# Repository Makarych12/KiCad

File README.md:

# KiCad Мастер Pro

Интерактивный курс проектирования печатных плат в KiCad 8–10: статический сайт (PWA) и serverless API для Vercel.

## Развёртывание на Vercel

1. **Импорт репозитория.** На [vercel.com/new](https://vercel.com/new) выберите репозиторий `Makarych12/KiCad`. Framework Preset: **Other**. Build Command и Output Directory оставьте пустыми: сайт статический, функции лежат в `api/`.
2. **Хранилище.** Project → Storage → Marketplace → **Upstash Redis** (это бывший Vercel KV) → Connect к проекту. Vercel сам добавит переменные `KV_REST_API_URL` и `KV_REST_API_TOKEN`.
3. **AI-ассистент.** Project → Settings → Environment Variables → `OPENROUTER_API_KEY` (ключ `sk-or-…` с openrouter.ai/keys) **или** `ANTHROPIC_API_KEY` (console.anthropic.com). Модель по умолчанию — Claude Opus 5 (`anthropic/claude-opus-5` на OpenRouter); другую можно задать через `KM_MODEL`. Необязательно, без ключа сайт работает.
4. **Deploy** или Redeploy после добавления переменных. Каждый следующий `git push` в `main` деплоится автоматически.
5. **Проверка.** Откройте `https://<ваш-проект>.vercel.app/api/health`. Должно быть `"storage":"redis"` и, если задан ключ, `"ai":true`.

**Выбор модели.** На странице `/models` посетитель выбирает модель для ассистента. Сайт разрешает только модели не дороже `KM_MAX_PRICE` долларов за 1 млн токенов вывода (по умолчанию 30). Можно задать и явный список `KM_ALLOWED_MODELS`, например `anthropic/*,google/gemini-2.5-flash`. Так посетители не потратят баланс ключа на дорогие модели.

Все переменные описаны в `.env.example`. Если Redis не подключён, API работает, но данные живут только в памяти функции и пропадают при перезапуске. Статус «хранилище в памяти» виден в Настройках сайта.

### API (`api/*.js`, общий код — `lib/`)

| Эндпоинт | Методы | Назначение |
|---|---|---|
| `/api/chat` | POST | AI-ассистент (Claude через Anthropic или OpenRouter, потоковый ответ SSE) |
| `/api/messages` | GET `?since=`, POST | Чат сообщества (опрос раз в 4 с) |
| `/api/leaderboard` | GET, POST | Таблица лидеров |
| `/api/submit-project` | GET, POST, POST `?action=rate&id=` | Галерея проектов и рейтинг |
| `/api/file` | GET `?id=&kind=` | Скачивание файлов галереи |
| `/api/sync` | GET, PUT | Синхронизация прогресса |
| `/api/register` | GET, POST | Вход по нику (токен) |
| `/api/newsletter` | POST | Подписка на рассылку |
| `/api/models` | GET | Каталог моделей OpenRouter с отметкой доступности (кэш 1 ч) |
| `/api/health` | GET | Состояние (AI, провайдер, тип хранилища) |

У всех эндпоинтов CORS: по умолчанию `*`, ограничить можно через `ALLOWED_ORIGIN`. Лимиты частоты считаются в Redis.

## Локальный запуск

```bash
npm install
npm run dev                      # http://localhost:8080 — статика + те же функции из api/
OPENROUTER_API_KEY=sk-or-... npm run dev   # или ANTHROPIC_API_KEY=sk-ant-...
npm run test:api                 # тест всех эндпоинтов: с имитацией Upstash Redis и с локальным хранилищем
```

Локально без Redis данные сохраняются в `.data/db.json`. Переменные можно положить в `.env`: сервер прочитает его сам.

## Что внутри

| Раздел | Где | Что сделано |
|---|---|---|
| 1. Уроки | `data/lessons*.js` | 56 уроков (44 базовых, 8 продвинутых, 4 бонусных): шаги, аннотированные иллюстрации, советы, ошибки, тест из 5 вопросов |
| 2. Видео | `data/demos.js`, `js/views/demos.js` | 8 анимированных демонстраций: главы, пауза, перемотка, скорость 0,25–2×. Можно подключить настоящие mp4 |
| 3. Практика | `tools/projects.py` → `kicad/pXX*` | 16 проектов: заготовка KiCad, эталон, автопроверка netlist по цепям и номиналам, медали |
| 4. Компоненты | `data/components.js` | 1182 позиции: 174 описаны вручную, остальное — ряды E24/E6, стабилитроны, светодиоды, разъёмы |
| 5. Шаблоны | `tools/circuits.py` → `kicad/t-*` | 26 проектов KiCad: .kicad_pro/.kicad_sch, PDF, BOM, SVG-превью, netlist |
| 6. Симулятор | `js/sim.js`, `js/views/sim.js` | Метод узловых потенциалов, Ньютон для диодов и светодиодов, переходные процессы для конденсаторов |
| Gerber и 3D | `js/gerber-parse.js`, `js/views/gerber.js` | Разбор Gerber RS-274X/X2 (макросы, дуги, полигоны), Excellon и ZIP в браузере; виды «Верх», «Низ», «Слои», 3D; линейка; проверка перед заказом. Демо-платы — настоящие Gerber из KiCad (`tools/pcbgen.py`) |
| Тренажёр трассировки | `js/routing-engine.js`, `js/views/routing.js` | 5 уровней: дорожки под 45°, зазоры, силовые цепи, два слоя и переходы, DRC и проверка связности, звёзды и опыт |
| 7. Тесты | в уроках | Очки, медали, достижения, таблица лидеров (через сервер) |
| 8. История | `data/history.js` | 5 статей, хронология, персоналии |
| 9. Справочник | `data/reference.js`, `js/views/reference.js` | Горячие клавиши, ряды E, цветовой код, типоразмеры, слои, 14 калькуляторов, глоссарий |
| 10. Сообщество | `js/views/community.js`, `api/` | AI-ассистент (Claude), чат, галерея с рейтингом, рассылка |
| 11. Продвинутые темы | `data/lessons-adv.js` | ВЧ, ЭМС, DFM, Python, Arduino, Raspberry Pi, ESP32, 4 слоя |
| 12. Геймификация | `js/core.js`, `data/achievements.js` | Опыт, 36 достижений, уровни, бонусные уроки, серия дней, тепловая карта |
| 13. PWA | `manifest.webmanifest`, `sw.js` | Установка на телефон, офлайн, полное скачивание материалов |
| 14. Экспорт | `js/views/profile.js` | Уроки в PDF, закладки, заметки, резервная копия/синхронизация, сертификат PNG/PDF |
| AI-ассистент | `js/assistant.js`, `js/views/models.js` | Кнопка «Спросить AI» на всех страницах, контекст текущей страницы, каталог моделей OpenRouter с фильтрами и выбором |
| Прочее | `js/views/settings.js` | Тёмная/светлая тема, акцентный цвет, размер шрифта, высокий контраст, язык интерфейса (RU/EN/UK), напоминания |

## Как обновлять

- **Схемы и проекты KiCad:** правьте `tools/circuits.py` / `tools/projects.py`, затем выполните `python3 tools/build.py`. Скрипт генерирует проекты, прогоняет ERC в `kicad-cli`, сверяет netlist с задуманными цепями, экспортирует SVG/PDF/BOM и обновляет `data/kicad-gen.js`. Нужен установленный KiCad 8+.
- **Демо-платы просмотрщика Gerber:** правьте `tools/pcbgen.py` и выполните `python3 tools/pcbgen.py` — он соберёт `.kicad_pcb`, проверит DRC в `kicad-cli` и выгрузит `kicad/*-gerber.zip`.
- **Тесты без браузера:** `node tools/test-gerber.mjs` (разбор Gerber/Excellon/ZIP на демо-платах) и `node tools/test-routing.mjs` (эталонные решения уровней тренажёра проходят DRC, ошибки ловятся).
- **После любых изменений файлов:** выполните `python3 tools/make_sw.py`. Он обновит версию офлайн-кэша и `assets.json`.
- **Настоящие скриншоты KiCad:** положите PNG в `media/screens/` и пропишите их в `KM.data.screens` (`data/figures.js`). Аннотации наложатся поверх.
- **Настоящие видео:** положите mp4 в `media/videos/` и добавьте демо поле `video: 'media/videos/имя.mp4'`.

## Ограничения, о которых стоит знать

- Иллюстрации интерфейса — схематичные SVG-перерисовки окон KiCad, а не скриншоты. Реальный рендер KiCad есть только у схем-шаблонов и проектов.
- Изображения компонентов тоже схематичные, цены ориентировочные. Ссылки ведут на поиск у поставщиков и в базах даташитов.
- Схемы оформлены «метками цепей» (у каждого вывода — провод и имя цепи). Это полноценные схемы, но выглядят иначе, чем нарисованные вручную.
- Для плат (`.kicad_pcb`), Gerber и 3D-моделей нужна разводка человеком. В проектах есть схема, BOM и netlist, а плата делается командой F8 по урокам.
- Вход упрощённый (ник + токен), модерации чата нет. Для открытого публичного сайта стоит добавить настоящую аутентификацию и модерацию.
- Файлы галереи хранятся в Redis, поэтому лимит — 700 КБ на файл. Для больших архивов лучше подключить Vercel Blob.
- Чат обновляется опросом раз в 4 секунды: serverless-функции не держат постоянных соединений.
- Учебные тексты — только на русском, переводится интерфейс.

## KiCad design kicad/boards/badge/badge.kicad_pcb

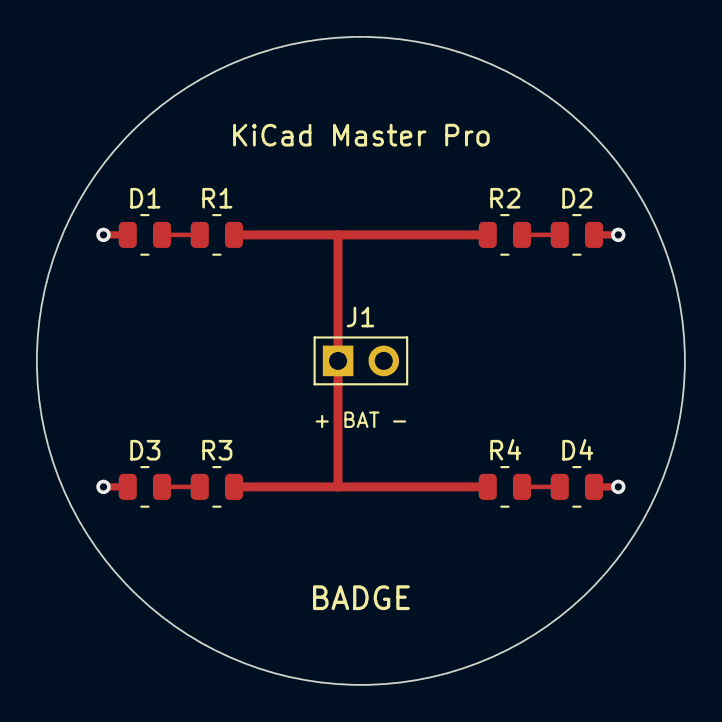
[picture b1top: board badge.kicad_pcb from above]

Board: 2 copper layers, 36.0 x 36.0 mm, 9 parts (0 on the bottom side), 6 nets.

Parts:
D1, D2, D3, D4: LED; R_0805
J1: BAT; PinHeader_1x02
R1, R2, R3, R4: 330; R_0805

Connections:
GND: D1.1, D2.2, D3.1, D4.2, J1.2
LED1: D1.2, R1.1
LED2: D2.1, R2.2
LED3: D3.2, R3.1
LED4: D4.1, R4.2
VCC: J1.1, R1.2, R2.1, R3.2, R4.1

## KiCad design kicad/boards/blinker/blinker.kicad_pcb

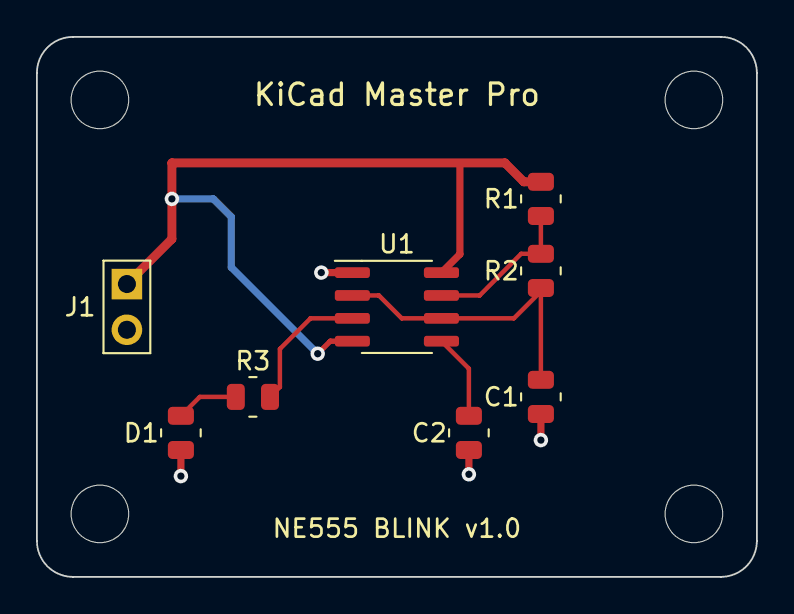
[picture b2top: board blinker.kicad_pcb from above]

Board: 2 copper layers, 40.0 x 30.0 mm, 12 parts (0 on the bottom side), 7 nets.

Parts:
C1: 10u; R_0805_V
C2: 10n; R_0805_V
D1: LED; R_0805_V
H: MountingHole
H#2, H#3, H#4: MountingHole
J1: 5V; PinHeader_1x02
R1: 10k; R_0805_V
R2: 47k; R_0805_V
R3: 470; R_0805
U1: NE555; SOIC-8

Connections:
CTRL: C2.1, U1.5
DISCH: R1.2, R2.1, U1.7
GND: C1.2, C2.2, D1.2, J1.2, U1.1
LED: D1.1, R3.1
OUT: R3.2, U1.3
THRES: C1.1, R2.2, U1.2, U1.6
VCC: J1.1, R1.1, U1.4, U1.8
